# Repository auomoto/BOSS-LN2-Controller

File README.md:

# BOSS-LN2-Controller
## Liquid Nitrogen Fill Controller for the LCO BOSS Spectrograph
This separate unit automatically fills the small CCD dewars on the BOSS Spectrographs from a larger buffer dewar installed on the telescope rotator. That buffer dewar is filled twice a day (dusk, dawn).

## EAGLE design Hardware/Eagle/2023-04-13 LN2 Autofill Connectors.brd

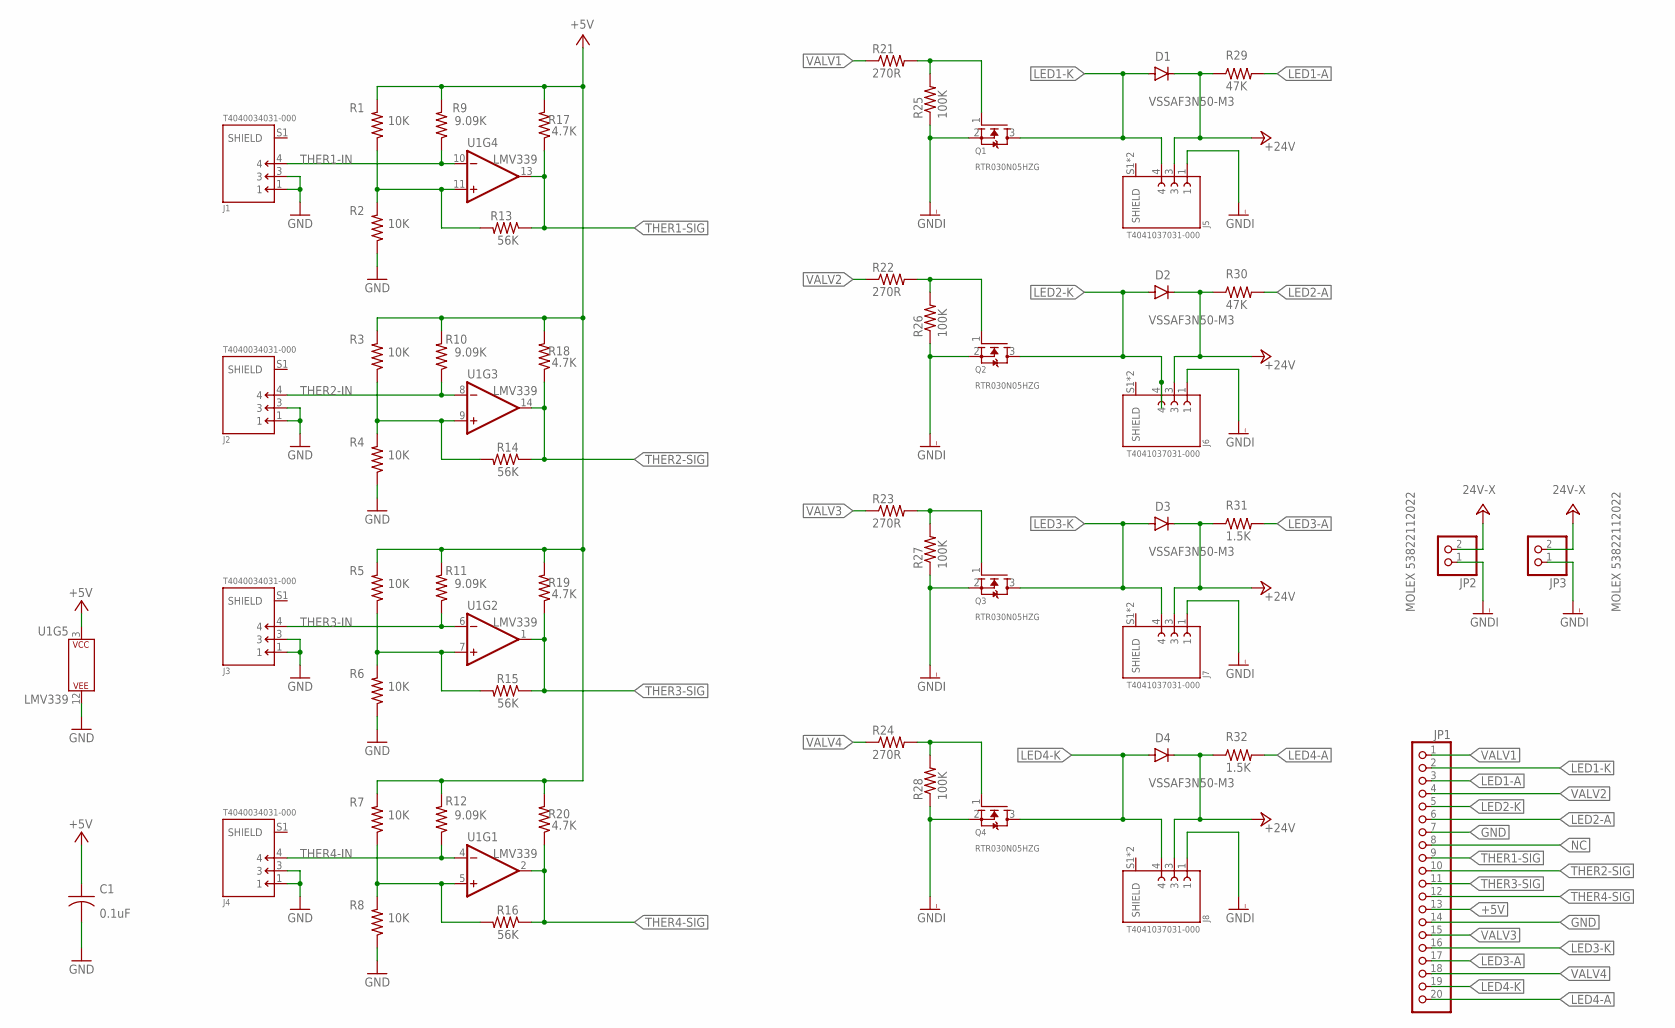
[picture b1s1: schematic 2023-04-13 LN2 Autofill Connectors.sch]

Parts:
C1: 0.1uF; C0805
D1, D2, D3, D4: VSSAF3N50-M3; SMA-DO214AC
J1, J2, J3, J4: T4040034031-000; TE_T4040034031-000
J5, J6, J7, J8: T4041037031-000; TE_T4041037031-000
JP1: PINHD-1X20; 1X20
JP2, JP3: MOLEX 53822112022; MOLEX-02-VERT
Q1, Q2, Q3, Q4: RTR030N05HZG; SOT23
R1, R2, R3, R4, R5, R6, R7, R8: 10K; R0805
R9, R10, R11, R12: 9.09K; R0805
R13, R14, R15, R16: 56K; R0805
R17, R18, R19, R20: 4.7K; R0805
R21, R22, R23, R24: 270R; R0805
R25, R26, R27, R28: 100K; R0805
R29, R30: 47K; R0805
R31, R32: 1.5K; R0805
U1: LMV339; SOIC127P599X175-14

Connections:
+5V: C1.1, JP1.13, R1.2, R3.2, R5.2, R7.2, R9.2, R10.2, R11.2, R12.2, R17.2, R18.2, R19.2, R20.2, U1.3 (P$V+)
+24V: D1.K (C), D2.K (C), D3.K (C), D4.K (C), J5.3, J6.3, J7.3, J8.3, JP2.2, JP3.2, R29.1, R30.1, R31.1, R32.1
GND: C1.2, J1.1, J1.3, J2.1, J2.3, J3.1, J3.3, J4.1, J4.3, JP1.7, JP1.14, R2.1, R4.1, R6.1, R8.1, U1.12 (P$V-)
GNDI: J5.1, J6.1, J7.1, J8.1, JP2.1, JP3.1, Q1.2 (S), Q2.2 (S), Q3.2 (S), Q4.2 (S), R25.1, R26.1, R27.1, R28.1
LED1-A: JP1.3, R29.2
LED1-K: D1.A, J5.4, JP1.2, Q1.3 (D)
LED2-A: JP1.6, R30.2
LED2-K: D2.A, J6.4, JP1.5, Q2.3 (D)
LED3-A: JP1.17, R31.2
LED3-K: D3.A, J7.4, JP1.16, Q3.3 (D)
LED4-A: JP1.20, R32.2
LED4-K: D4.A, J8.4, JP1.19, Q4.3 (D)
unnamed: Q1.1 (G), R21.2, R25.2
unnamed: Q2.1 (G), R22.2, R26.2
unnamed: Q3.1 (G), R23.2, R27.2
unnamed: Q4.1 (G), R24.2, R28.2
NC: JP1.8
THER1-IN: J1.4, R9.1, U1.10 (-IN)
THER1-SIG: JP1.9, R13.1, R17.1, U1.13 (OUT)
THER2-IN: J2.4, R10.1, U1.8 (-IN)
THER2-SIG: JP1.10, R14.1, R18.1, U1.14 (OUT)
THER3-IN: J3.4, R11.1, U1.6 (-IN)
THER3-SIG: JP1.11, R15.1, R19.1, U1.1 (OUT)
THER4-IN: J4.4, R12.1, U1.4 (-IN)
THER4-SIG: JP1.12, R16.1, R20.1, U1.2 (OUT)
TRIM1: R1.1, R2.2, R13.2, U1.11 (+IN)
TRIM2: R3.1, R4.2, R14.2, U1.9 (+IN)
TRIM3: R5.1, R6.2, R15.2, U1.7 (+IN)
TRIM4: R7.1, R8.2, R16.2, U1.5 (+IN)
VALV1: JP1.1, R21.1
VALV2: JP1.4, R22.1
VALV3: JP1.15, R23.1
VALV4: JP1.18, R24.1

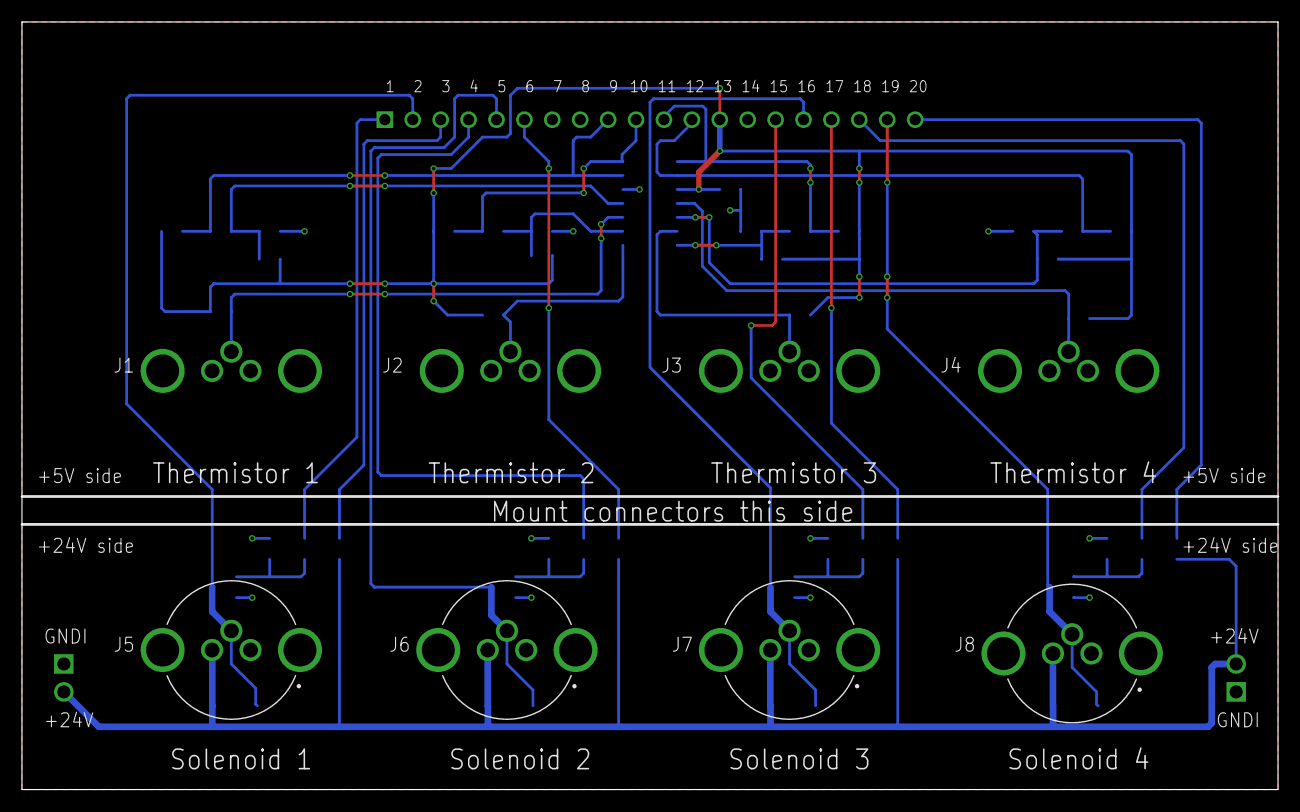
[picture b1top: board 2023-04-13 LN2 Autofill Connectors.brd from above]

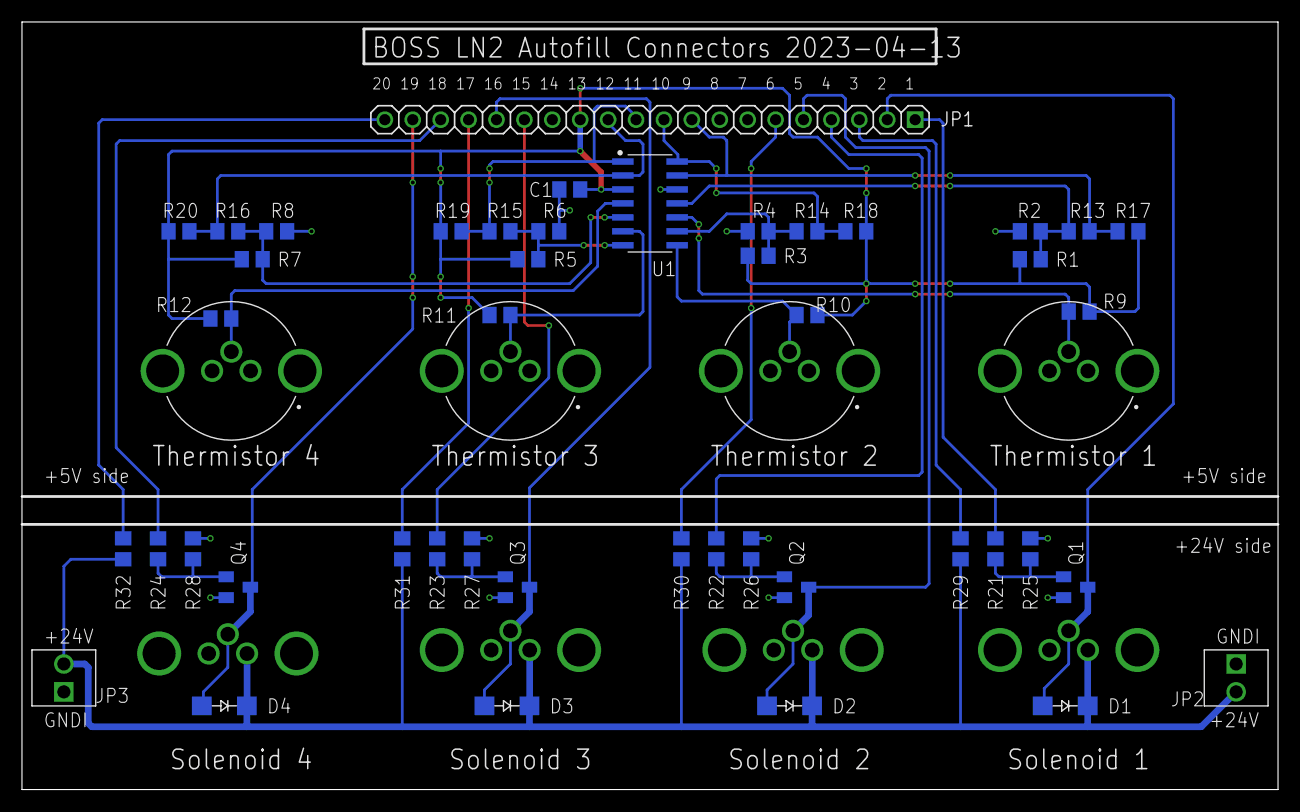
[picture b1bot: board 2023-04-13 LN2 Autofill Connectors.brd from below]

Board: 2 copper layers, 114.3 x 69.8 mm, 53 parts (45 on the bottom side), 32 nets.

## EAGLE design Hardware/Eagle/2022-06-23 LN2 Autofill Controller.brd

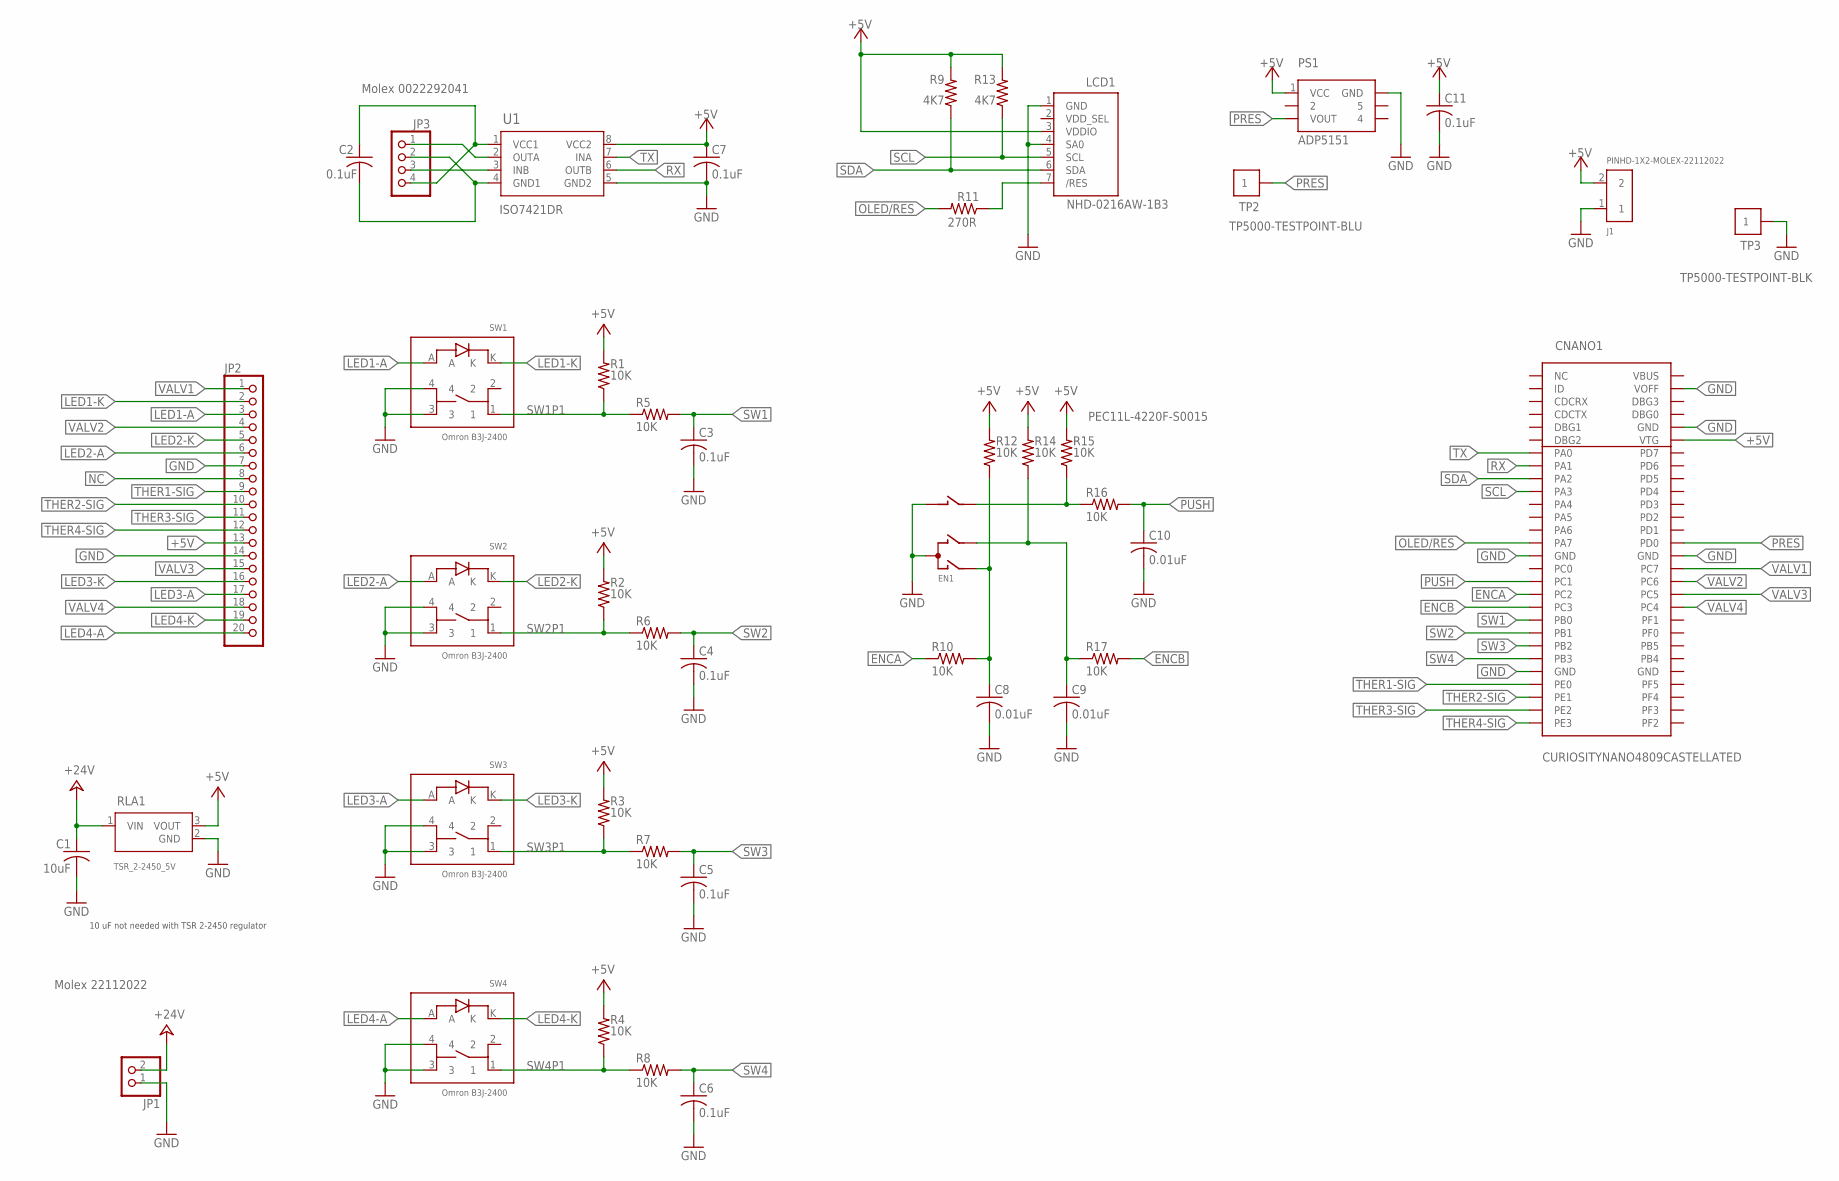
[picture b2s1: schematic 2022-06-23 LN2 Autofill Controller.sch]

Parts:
C1: 10uF; C1210K
C2, C3, C4, C5, C6, C7, C11: 0.1uF; C0805
C8, C9, C10: 0.01uF; C0805
CNANO1: CURIOSITYNANO4809CASTELLATED
EN1: PEC11L-4220F-S0015; ENC-BOURNES-PEC11L
J1: PINHD-1X2-MOLEX-22112022; 1X02-MOLEX-22112022
JP1: Molex 22112022; MOLEX-02-VERT
JP2: PINHD-1X20; 1X20
JP3: Molex 0022292041; MOLEX-04-VERT
LCD1: NHD-0216AW-1B3; LCD-NEWHAVEN-16X2
PS1: ADP5151; PRESSURE-SENSOR-ADP5151
R1, R2, R3, R4, R5, R6, R7, R8, R10, R12, R14, R15, R16, R17: 10K; R0805
R9, R13: 4K7; R0805
R11: 270R; R0805
RLA1: TSR_2-2450_5V; TSR2-SINGLE_TRP
SW1, SW2, SW3, SW4: Omron B3J-2400; SWITCH-OMRON-B3J-1LED
TP2: TP5000-TESTPOINT-BLU
TP3: TP5000-TESTPOINT-BLK
U1: ISO7421DR; SOIC127P599X175-8N

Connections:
+5V: C7.1, C11.1, CNANO1.VTG, J1.2, JP2.13, LCD1.3 (VDDIO), PS1.1 (VCC), R1.2, R2.2, R3.2, R4.2, R9.2, R12.2, R13.2, R14.2, R15.2, RLA1.3 (VOUT), U1.8 (VCC2)
+24V: C1.1, JP1.2, RLA1.1 (VIN)
/RES: LCD1.7 (/RES), R11.1
ENCA: CNANO1.PC2, R10.1
ENCASW: C8.1, EN1.A, R10.2, R12.1
ENCB: CNANO1.PC3, R17.2
ENCBSW: C9.1, EN1.B, R14.1, R17.1
ENCBUTTON: EN1.1 (B1), R15.1, R16.1
GND: C1.2, C3.2, C4.2, C5.2, C6.2, C7.2, C8.2, C9.2, C10.2, C11.2, CNANO1.GND15 (GND), CNANO1.GND24 (GND), CNANO1.GND42 (GND), CNANO1.GND52 (GND), CNANO1.VOFF, EN1.2 (C1), EN1.C, J1.1, JP1.1, JP2.7, JP2.14, LCD1.1 (GND), LCD1.4 (SA0), PS1.6 (GND), RLA1.2 (GND), SW1.3, SW1.4, SW2.3, SW2.4, SW3.3, SW3.4, SW4.3, SW4.4, TP3.P$1, U1.5 (GND2)
GND1: C2.2, JP3.2, U1.4 (GND1)
INB: JP3.3, U1.3 (INB)
LED1-A: JP2.3, SW1.A
LED1-K: JP2.2, SW1.K
LED2-A: JP2.6, SW2.A
LED2-K: JP2.5, SW2.K
LED3-A: JP2.17, SW3.A
LED3-K: JP2.16, SW3.K
LED4-A: JP2.20, SW4.A
LED4-K: JP2.19, SW4.K
NC: JP2.8
OLED/RES: CNANO1.PA7-SS (PA7), R11.2
OUTA: JP3.1, U1.2 (OUTA)
PRES: CNANO1.PD0-AIN0 (PD0), PS1.3 (VOUT), TP2.P$1
PUSH: C10.1, CNANO1.PC1-RX (PC1), R16.2
RX: CNANO1.PA1-RX (PA1), U1.6 (OUTB)
SCL: CNANO1.PA3-SCL (PA3), LCD1.5 (SCL), R13.1
SDA: CNANO1.PA2-SDA (PA2), LCD1.6 (SDA), R9.1
SW1: C3.1, CNANO1.PB0-TX (PB0), R5.2
SW1P1: R1.1, R5.1, SW1.1
SW2: C4.1, CNANO1.PB1-RX (PB1), R6.2
SW2P1: R2.1, R6.1, SW2.1
SW3: C5.1, CNANO1.PB2, R7.2
SW3P1: R3.1, R7.1, SW3.1
SW4: C6.1, CNANO1.PB3, R8.2
SW4P1: R4.1, R8.1, SW4.1
THER1-SIG: CNANO1.PE0, JP2.9
THER2-SIG: CNANO1.PE1, JP2.10
THER3-SIG: CNANO1.PE2, JP2.11
THER4-SIG: CNANO1.PE3, JP2.12
TX: CNANO1.PA0-TX (PA0), U1.7 (INA)
VALV1: CNANO1.PC7, JP2.1
VALV2: CNANO1.PC6, JP2.4
VALV3: CNANO1.PC5, JP2.15
VALV4: CNANO1.PC4, JP2.18
VCC1: C2.1, JP3.4, U1.1 (VCC1)

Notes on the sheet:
10 uF not needed with TSR 2-2450 regulator

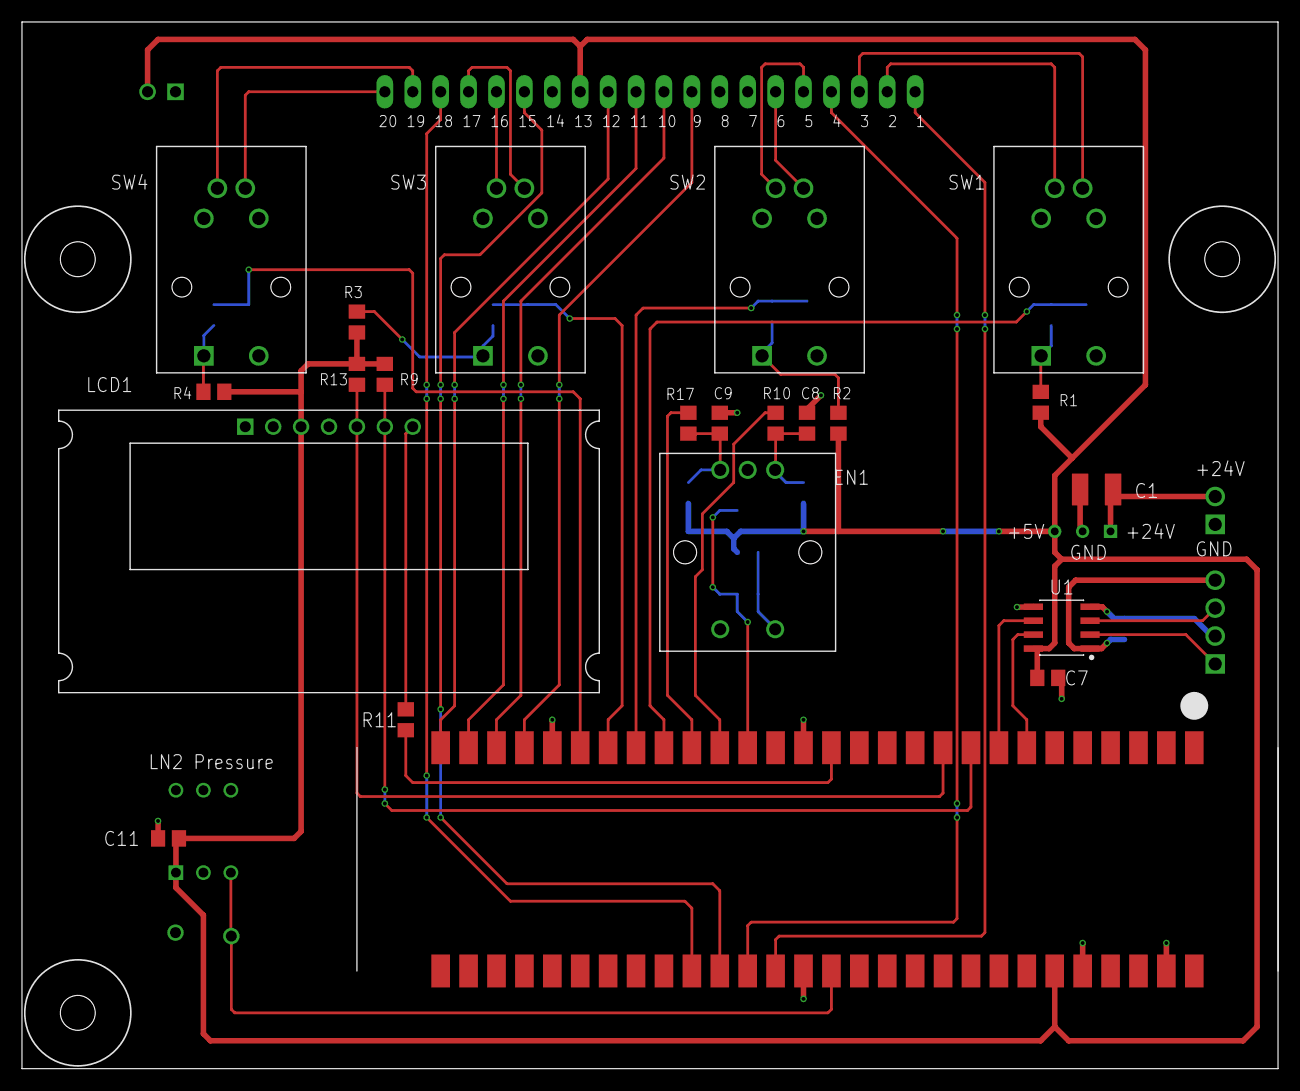
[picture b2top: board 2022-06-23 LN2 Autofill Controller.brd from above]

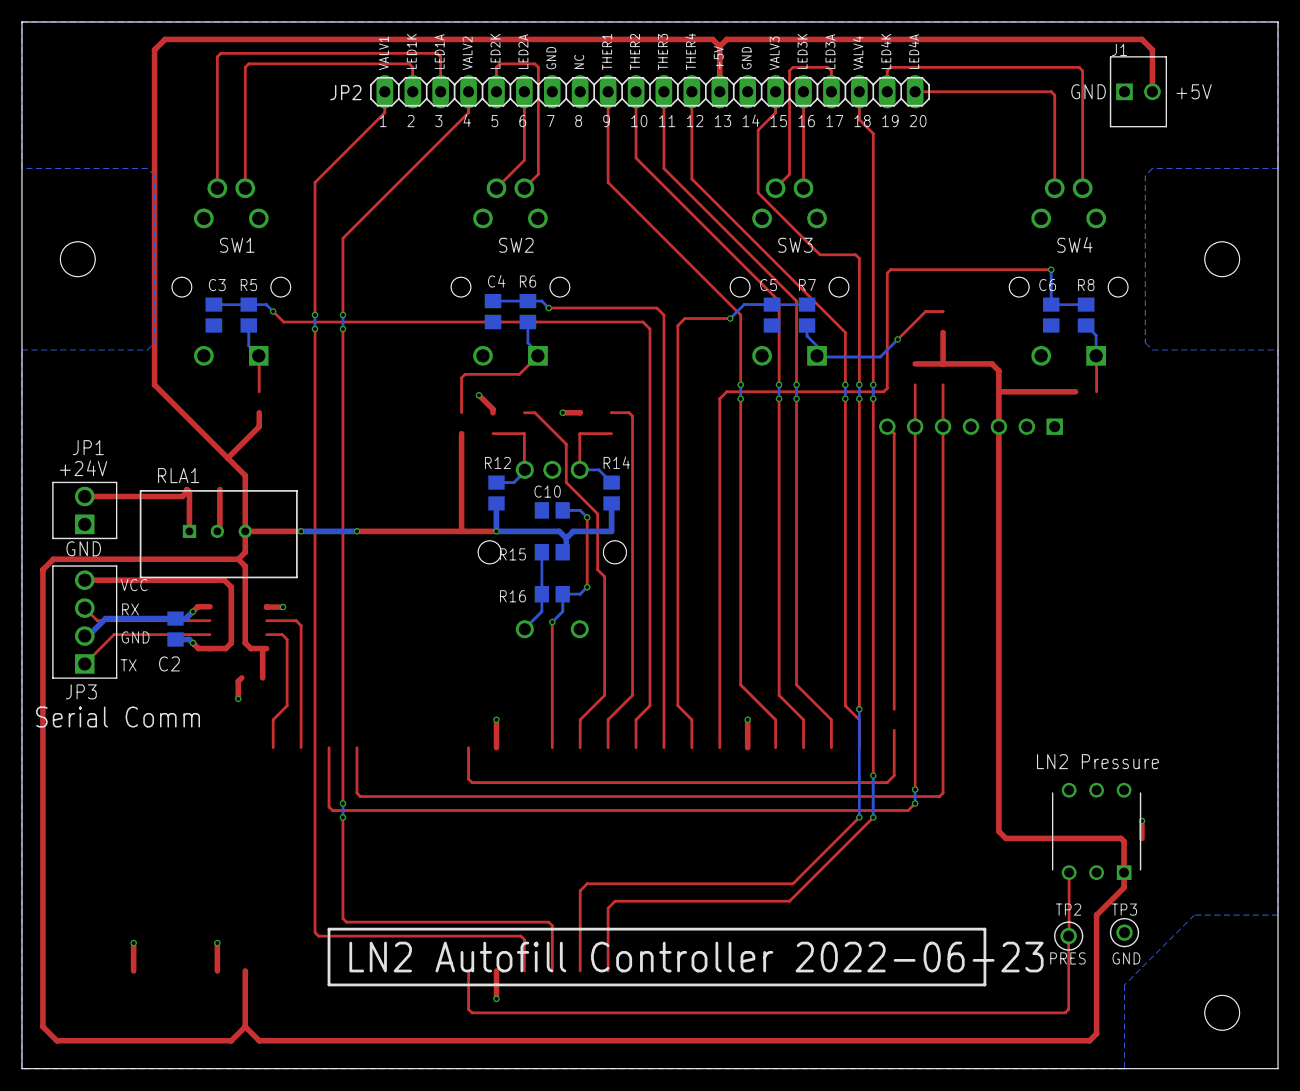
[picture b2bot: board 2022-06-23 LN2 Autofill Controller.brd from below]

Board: 2 copper layers, 114.3 x 95.2 mm, 44 parts (22 on the bottom side), 44 nets.

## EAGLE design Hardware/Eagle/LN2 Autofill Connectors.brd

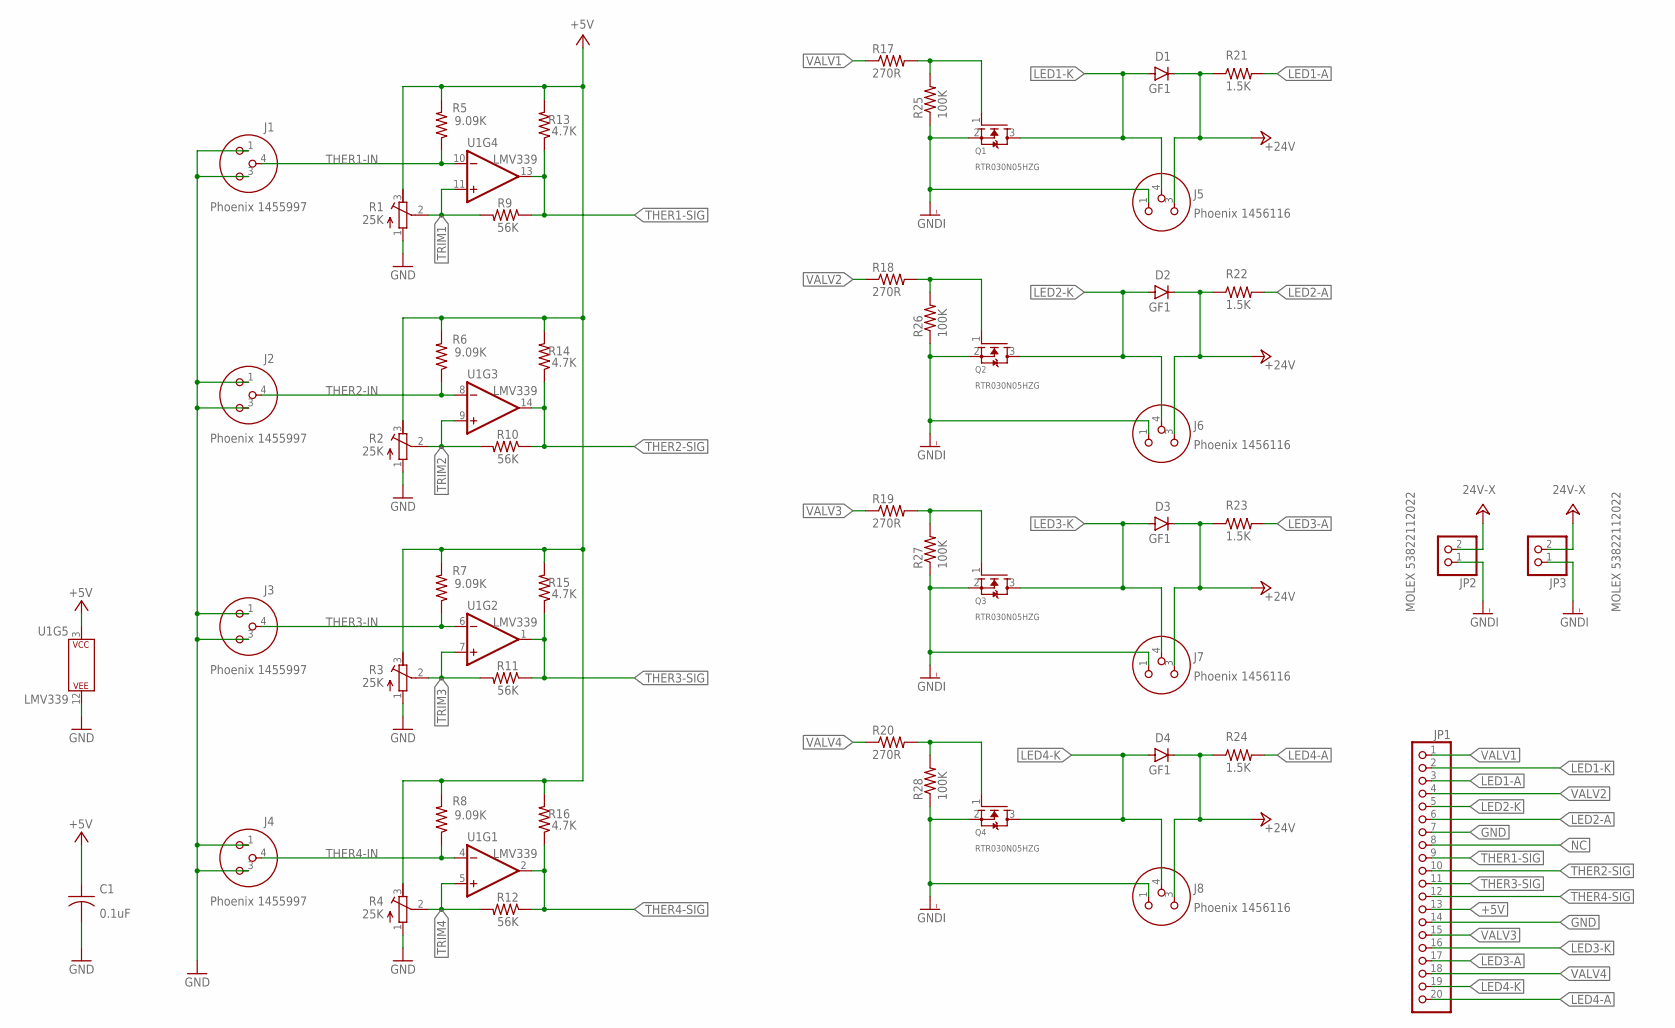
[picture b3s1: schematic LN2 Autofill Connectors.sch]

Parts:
C1: 0.1uF; C0805
D1, D2, D3, D4: GF1; SMA-DO214AC
J1, J2, J3, J4: Phoenix 1455997; PHOENIX-3PIN
J5, J6, J7, J8: Phoenix 1456116; PHOENIX-3PIN-FEMALE
JP1: PINHD-1X20; 1X20
JP2, JP3: MOLEX 53822112022; MOLEX-02-VERT
Q1, Q2, Q3, Q4: RTR030N05HZG; SOT23
R1, R2, R3, R4: 25K; RTRIM3296Y
R5, R6, R7, R8: 9.09K; R0805
R9, R10, R11, R12: 56K; R0805
R13, R14, R15, R16: 4.7K; R0805
R17, R18, R19, R20: 270R; R0805
R21, R22, R23, R24: 1.5K; R0805
R25, R26, R27, R28: 100K; R0805
U1: LMV339; SOIC127P599X175-14

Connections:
+5V: C1.1, JP1.13, R1.3 (E), R2.3 (E), R3.3 (E), R4.3 (E), R5.2, R6.2, R7.2, R8.2, R13.2, R14.2, R15.2, R16.2, U1.3 (P$V+)
+24V: D1.K (C), D2.K (C), D3.K (C), D4.K (C), J5.3, J6.3, J7.3, J8.3, JP2.2, JP3.2, R21.1, R22.1, R23.1, R24.1
GND: C1.2, J1.1, J1.3, J2.1, J2.3, J3.1, J3.3, J4.1, J4.3, JP1.7, JP1.14, R1.1 (A), R2.1 (A), R3.1 (A), R4.1 (A), U1.12 (P$V-)
GNDI: J5.1, J6.1, J7.1, J8.1, JP2.1, JP3.1, Q1.2 (S), Q2.2 (S), Q3.2 (S), Q4.2 (S), R25.1, R26.1, R27.1, R28.1
LED1-A: JP1.3, R21.2
LED1-K: D1.A, J5.4, JP1.2, Q1.3 (D)
LED2-A: JP1.6, R22.2
LED2-K: D2.A, J6.4, JP1.5, Q2.3 (D)
LED3-A: JP1.17, R23.2
LED3-K: D3.A, J7.4, JP1.16, Q3.3 (D)
LED4-A: JP1.20, R24.2
LED4-K: D4.A, J8.4, JP1.19, Q4.3 (D)
unnamed: Q1.1 (G), R17.2, R25.2
unnamed: Q2.1 (G), R18.2, R26.2
unnamed: Q3.1 (G), R19.2, R27.2
unnamed: Q4.1 (G), R20.2, R28.2
NC: JP1.8
THER1-IN: J1.4, R5.1, U1.10 (-IN)
THER1-SIG: JP1.9, R9.1, R13.1, U1.13 (OUT)
THER2-IN: J2.4, R6.1, U1.8 (-IN)
THER2-SIG: JP1.10, R10.1, R14.1, U1.14 (OUT)
THER3-IN: J3.4, R7.1, U1.6 (-IN)
THER3-SIG: JP1.11, R11.1, R15.1, U1.1 (OUT)
THER4-IN: J4.4, R8.1, U1.4 (-IN)
THER4-SIG: JP1.12, R12.1, R16.1, U1.2 (OUT)
TRIM1: R1.2 (S), R9.2, U1.11 (+IN)
TRIM2: R2.2 (S), R10.2, U1.9 (+IN)
TRIM3: R3.2 (S), R11.2, U1.7 (+IN)
TRIM4: R4.2 (S), R12.2, U1.5 (+IN)
VALV1: JP1.1, R17.1
VALV2: JP1.4, R18.1
VALV3: JP1.15, R19.1
VALV4: JP1.18, R20.1

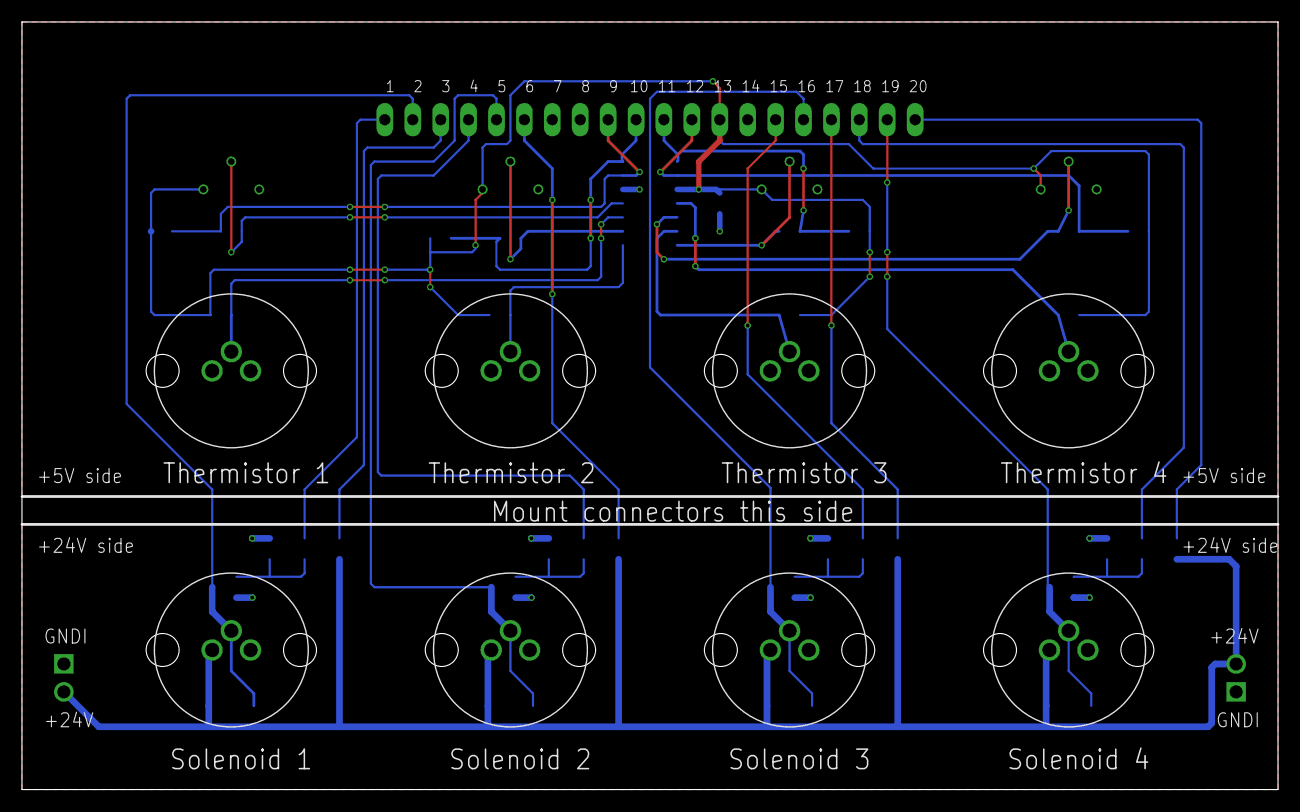
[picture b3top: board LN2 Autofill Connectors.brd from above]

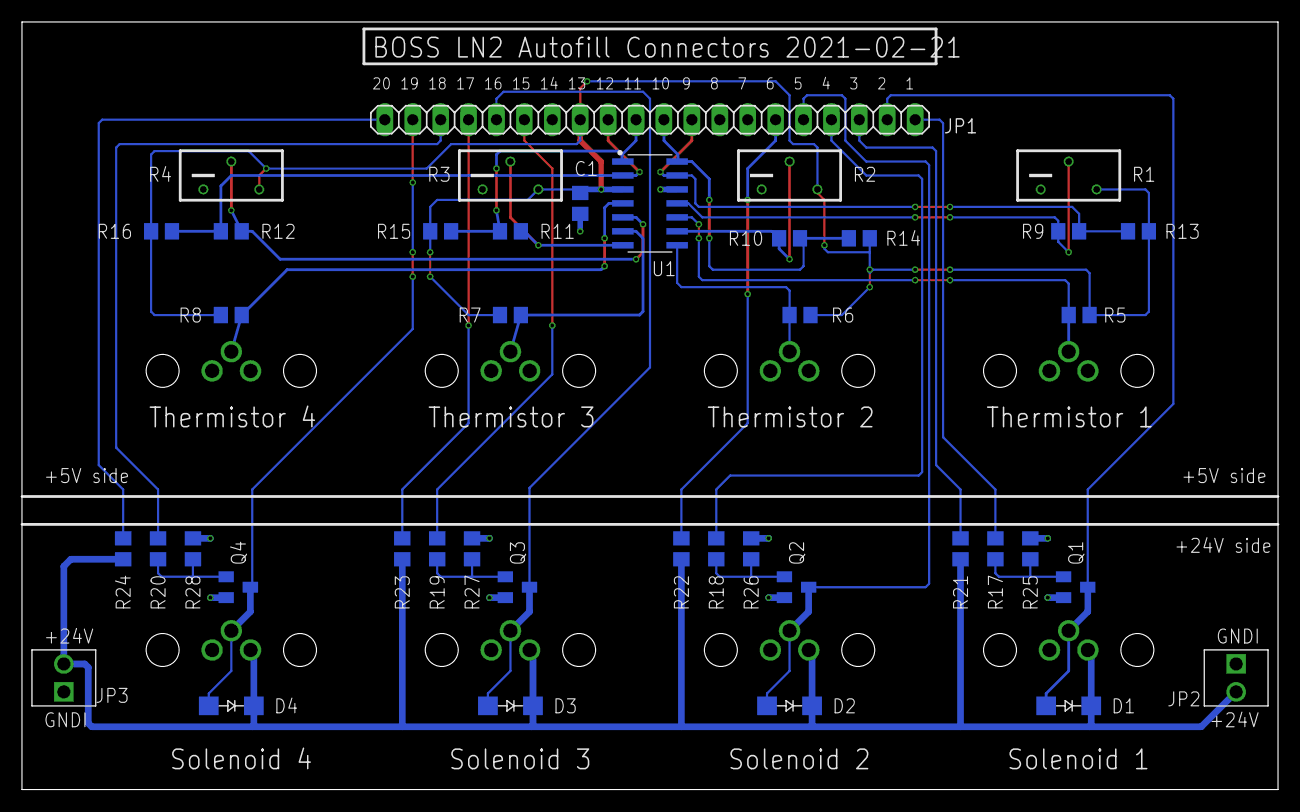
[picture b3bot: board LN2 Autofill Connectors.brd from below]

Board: 2 copper layers, 114.3 x 69.8 mm, 49 parts (41 on the bottom side), 32 nets.

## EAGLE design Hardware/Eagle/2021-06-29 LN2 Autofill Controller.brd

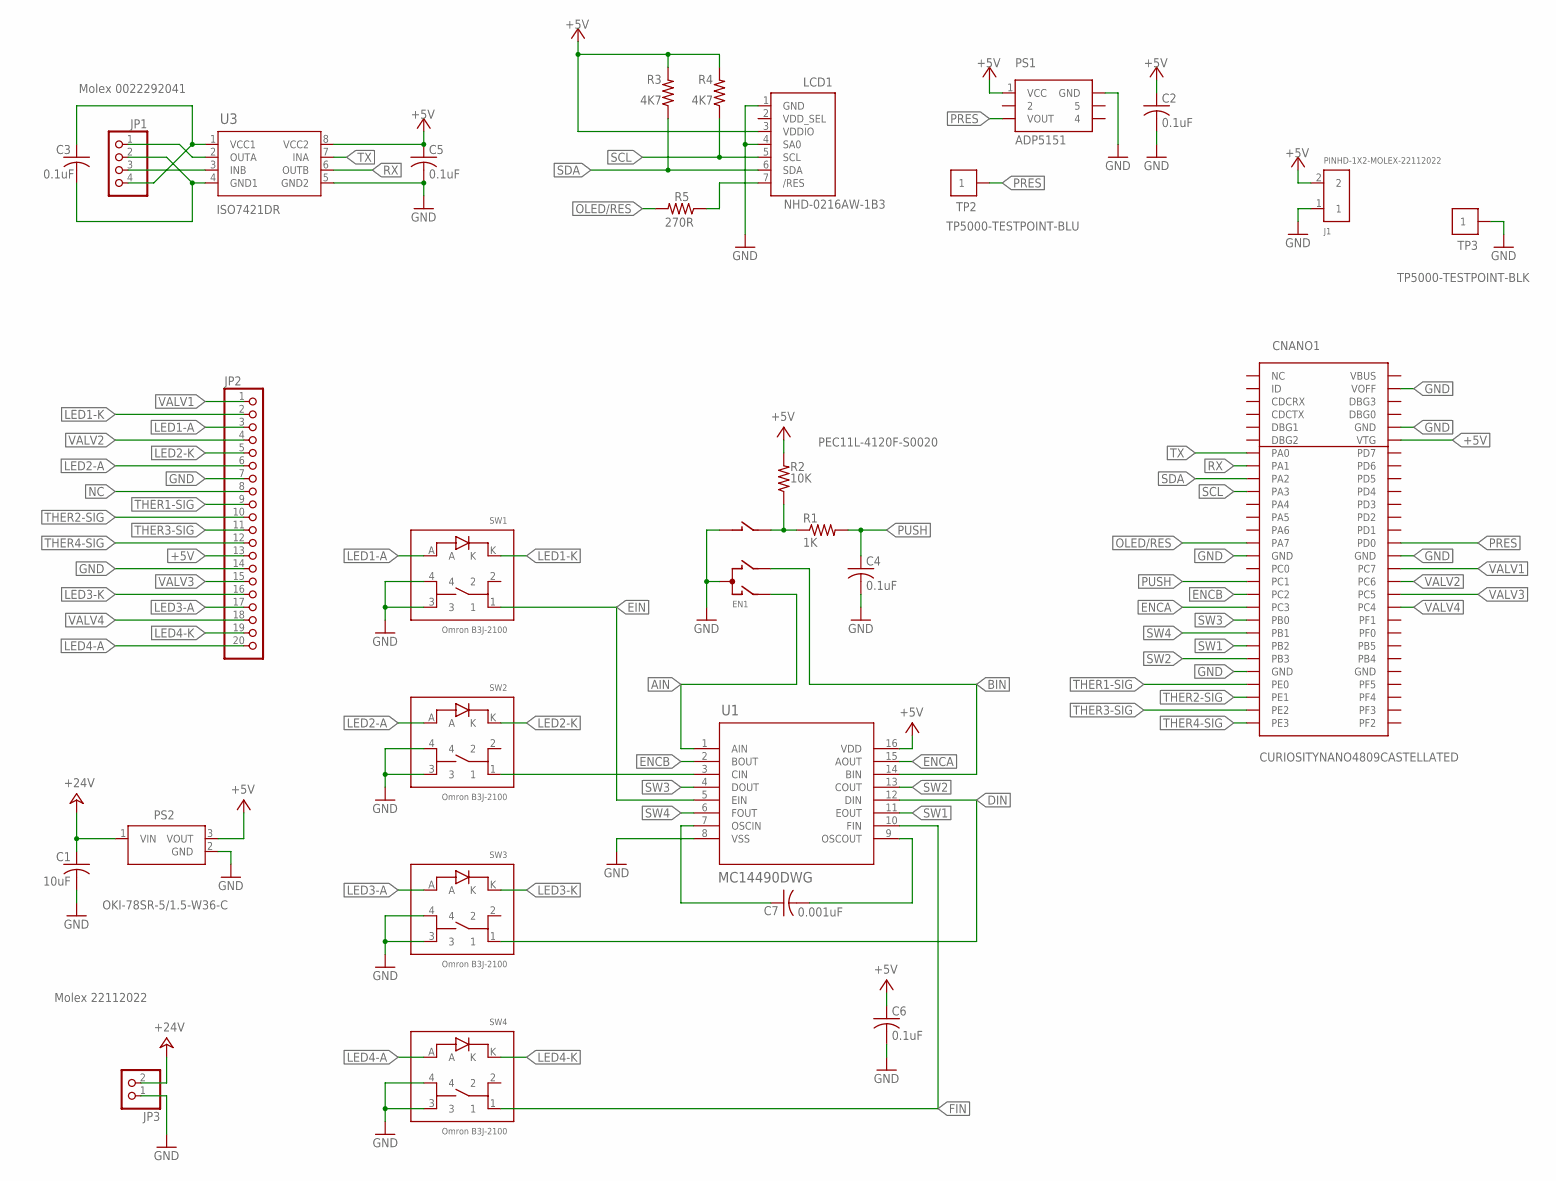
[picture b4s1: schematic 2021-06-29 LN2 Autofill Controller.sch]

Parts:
C1: 10uF; C1210K
C2, C3, C4, C5, C6: 0.1uF; C0805
C7: 0.001uF; C0805
CNANO1: CURIOSITYNANO4809CASTELLATED
EN1: PEC11L-4120F-S0020; ENC-BOURNES-PEC11L
J1: PINHD-1X2-MOLEX-22112022; 1X02-MOLEX-22112022
JP1: Molex 0022292041; MOLEX-04-VERT
JP2: PINHD-1X20; 1X20
JP3: Molex 22112022; MOLEX-02-VERT
LCD1: NHD-0216AW-1B3; LCD-NEWHAVEN-16X2
PS1: ADP5151; PRESSURE-SENSOR-ADP5151
PS2: OKI-78SR-5/1.5-W36-C; CONV_OKI-78SR-5/1.5-W36-C
R1: 1K; R0805
R2: 10K; R0805
R3, R4: 4K7; R0805
R5: 270R; R0805
SW1, SW2, SW3, SW4: Omron B3J-2100; SWITCH-OMRON-B3J-1LED
TP2: TP5000-TESTPOINT-BLU
TP3: TP5000-TESTPOINT-BLK
U1: MC14490DWG; SOIC127P1030X265-16N
U3: ISO7421DR; SOIC127P599X175-8N

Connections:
+5V: C2.1, C5.1, C6.1, CNANO1.VTG, J1.2, JP2.13, LCD1.3 (VDDIO), PS1.1 (VCC), PS2.3 (VOUT), R2.2, R3.2, R4.2, U1.16 (VDD), U3.8 (VCC2)
+24V: C1.1, JP3.2, PS2.1 (VIN)
/RES: LCD1.7 (/RES), R5.1
AIN: EN1.A, U1.1 (AIN)
BIN: EN1.B, U1.14 (BIN)
CIN: SW2.1, U1.3 (CIN)
DIN: SW3.1, U1.12 (DIN)
EIN: SW1.1, U1.5 (EIN)
ENCA: CNANO1.PC3, U1.15 (AOUT)
ENCB: CNANO1.PC2, U1.2 (BOUT)
ENCBUTTON: EN1.1 (B1), R1.1, R2.1
FIN: SW4.1, U1.10 (FIN)
GND: C1.2, C2.2, C4.2, C5.2, C6.2, CNANO1.GND15 (GND), CNANO1.GND24 (GND), CNANO1.GND42 (GND), CNANO1.GND52 (GND), CNANO1.VOFF, EN1.2 (C1), EN1.C, J1.1, JP2.7, JP2.14, JP3.1, LCD1.1 (GND), LCD1.4 (SA0), PS1.6 (GND), PS2.2 (GND), SW1.3, SW1.4, SW2.3, SW2.4, SW3.3, SW3.4, SW4.3, SW4.4, TP3.P$1, U1.8 (VSS), U3.5 (GND2)
GND1: C3.2, JP1.2, U3.4 (GND1)
INB: JP1.3, U3.3 (INB)
LED1-A: JP2.3, SW1.A
LED1-K: JP2.2, SW1.K
LED2-A: JP2.6, SW2.A
LED2-K: JP2.5, SW2.K
LED3-A: JP2.17, SW3.A
LED3-K: JP2.16, SW3.K
LED4-A: JP2.20, SW4.A
LED4-K: JP2.19, SW4.K
NC: JP2.8
OLED/RES: CNANO1.PA7-SS (PA7), R5.2
OSCIN: C7.1, U1.7 (OSCIN)
OSCOUT: C7.2, U1.9 (OSCOUT)
OUTA: JP1.1, U3.2 (OUTA)
PRES: CNANO1.PD0-AIN0 (PD0), PS1.3 (VOUT), TP2.P$1
PUSH: C4.1, CNANO1.PC1-RX (PC1), R1.2
RX: CNANO1.PA1-RX (PA1), U3.6 (OUTB)
SCL: CNANO1.PA3-SCL (PA3), LCD1.5 (SCL), R4.1
SDA: CNANO1.PA2-SDA (PA2), LCD1.6 (SDA), R3.1
SW1: CNANO1.PB2, U1.11 (EOUT)
SW2: CNANO1.PB3, U1.13 (COUT)
SW3: CNANO1.PB0-TX (PB0), U1.4 (DOUT)
SW4: CNANO1.PB1-RX (PB1), U1.6 (FOUT)
THER1-SIG: CNANO1.PE0, JP2.9
THER2-SIG: CNANO1.PE1, JP2.10
THER3-SIG: CNANO1.PE2, JP2.11
THER4-SIG: CNANO1.PE3, JP2.12
TX: CNANO1.PA0-TX (PA0), U3.7 (INA)
VALV1: CNANO1.PC7, JP2.1
VALV2: CNANO1.PC6, JP2.4
VALV3: CNANO1.PC5, JP2.15
VALV4: CNANO1.PC4, JP2.18
VCC1: C3.1, JP1.4, U3.1 (VCC1)

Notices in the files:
parts and their libraries:
AUmlib: COPYRIGHT: Copyright (C) 2016 Accelerated Designs. All rights reserved
COPYRIGHT: Copyright (C) 2022 Ultra Librarian. All rights reserved.
